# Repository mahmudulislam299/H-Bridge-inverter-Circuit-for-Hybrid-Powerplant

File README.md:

# H-Bridge-inverter-Circuit-for-Hybrid-Powerplant
This project aims is to design and construct a quite simple, efficient and low cost inverter with
high output capabilities to power some selected domestic appliances such lighting system,
small fan.
Our projects consists of three parts.
1) Converting and storing solar energy into a dc battery
2) Converting the stored dc into ac in the output side
3) Using this ac output to drive up to 30 watt ac load

Project Report: https://github.com/mahmudulislam299/H-Bridge-inverter-Circuit-for-Hybrid-Powerplant/blob/master/report.pdf

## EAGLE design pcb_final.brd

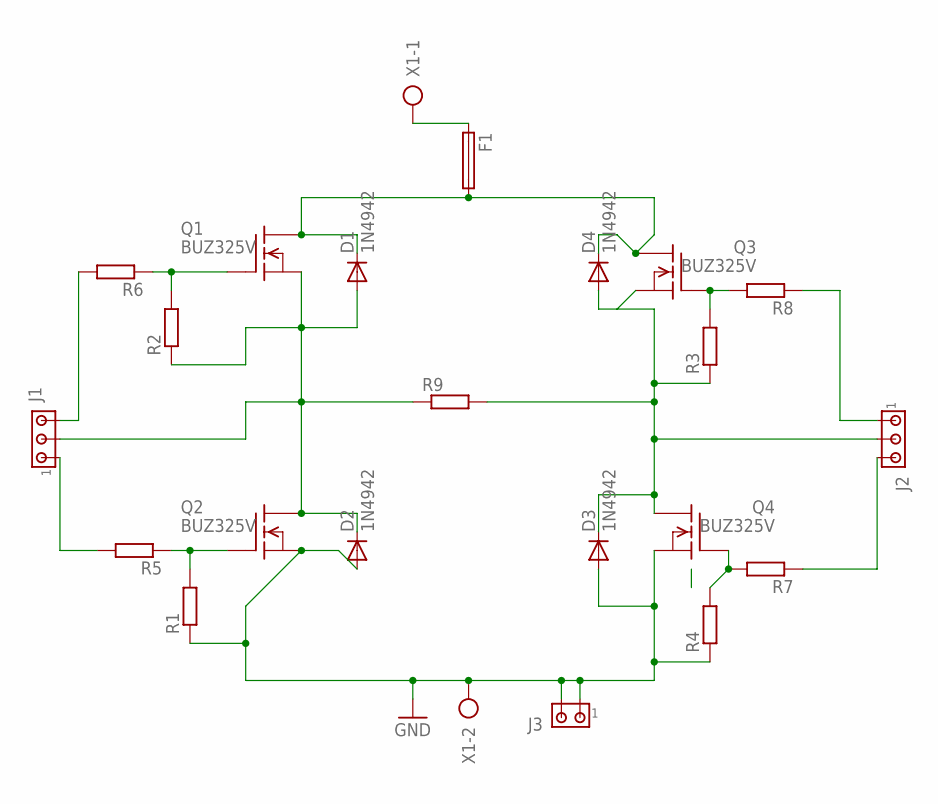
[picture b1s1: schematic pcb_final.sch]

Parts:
D1, D2, D3, D4: 1N4942; DO41-10
F1: 19560
J1, J2: MTA03-100; 10X03MTA
J3: MTA02-100; 10X02MTA
Q1, Q2, Q3, Q4: BUZ325V; TO218V
R1, R2, R3, R4, R5, R6, R7, R8, R9: R-EU_0207/10; 0207/10
X1: AK300/2

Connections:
GND: D2.A, D3.A, J3.1, J3.2, Q2.3 (S), Q4.3 (S), R1.1, R4.1, X1.2
unnamed: J1.3, R6.2
unnamed: Q1.1 (G), R2.2, R6.1
unnamed: J1.1, R5.2
unnamed: J2.3, R7.1
unnamed: Q2.1 (G), R1.2, R5.1
unnamed: D1.C, D4.C, F1.2, Q1.2 (D), Q3.2 (D)
unnamed: Q4.1 (G), R4.2, R7.2
unnamed: D1.A, D2.C, J1.2, Q1.3 (S), Q2.2 (D), R2.1, R9.1
unnamed: Q3.1 (G), R3.2, R8.2
unnamed: F1.1, X1.1
unnamed: J2.1, R8.1
unnamed: D3.C, D4.A, J2.2, Q3.3 (S), Q4.2 (D), R3.1, R9.2

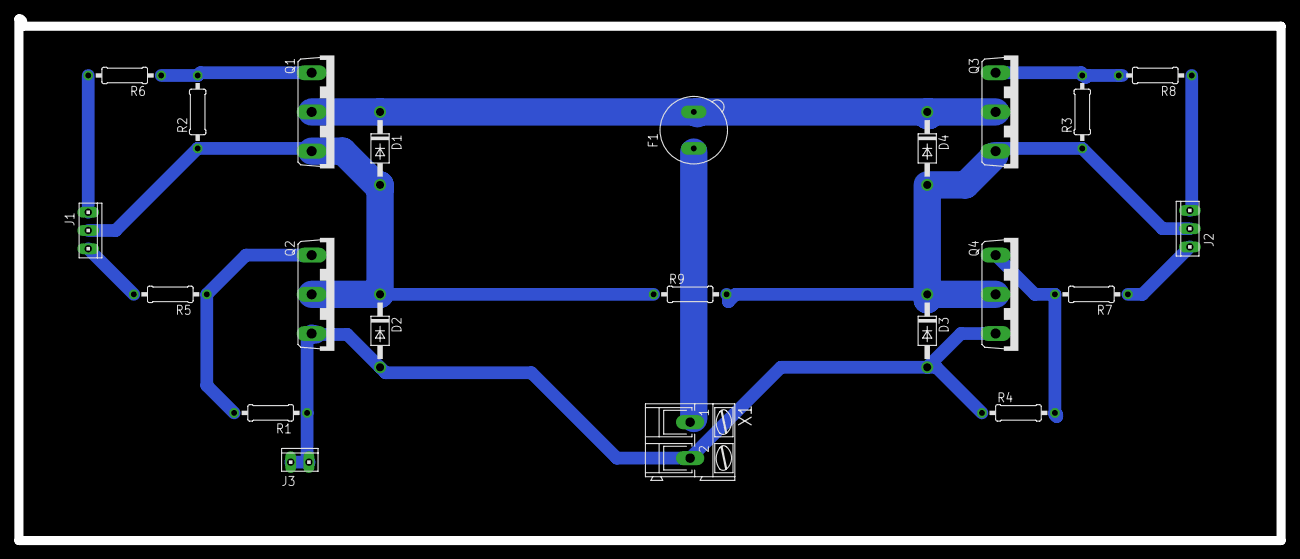
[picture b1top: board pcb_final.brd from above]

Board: 2 copper layers, 175.8 x 72.6 mm, 22 parts (0 on the bottom side), 13 nets.
